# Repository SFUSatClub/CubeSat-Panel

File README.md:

# CubeSat Panel
KiCad project of the panels located on the outside of the spacecraft.

This repository uses the SFU Satellite Team's KiCad component library as a submodule.
To start working on the repository:

```
1. Open the git shell
2. Navigate to the directory you wish to place the repository inside
3. git clone --recursive "https://github.com/SFUSatClub/CubeSat-Panel.git"
4. cd CubeSat-Panel/KiCad-Lib
5. git checkout master
```

If you modify either the component schematic or footprint libraries you must push those changes to the SFUSatClub/KiCad-Lib repository.

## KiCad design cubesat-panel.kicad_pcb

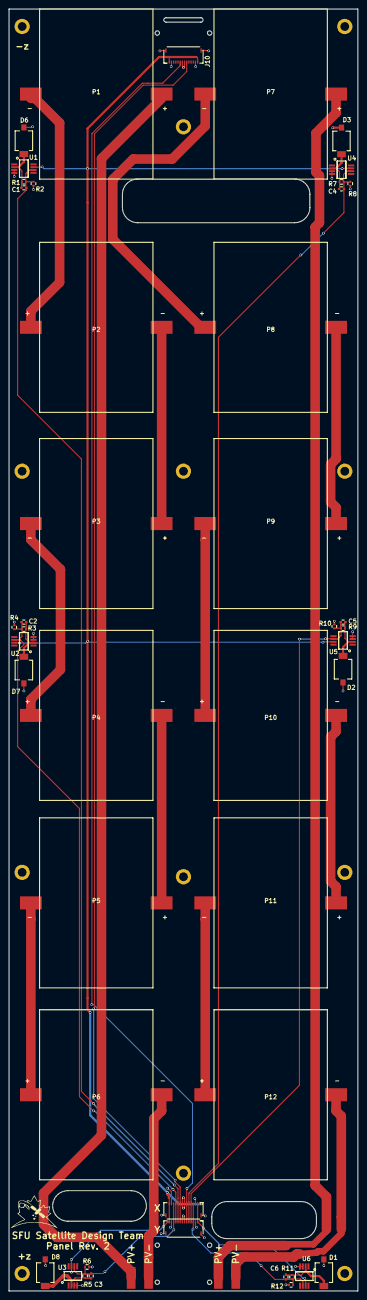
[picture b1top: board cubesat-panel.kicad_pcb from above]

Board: 2 copper layers, 80.0 x 294.0 mm, 61 parts (0 on the bottom side), 30 nets.

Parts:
C1, C2, C3, C4, C5, C6: 0.1uF; C_0402
D1, D2, D3, D4, D5, D6: D_Photo; SFH2430
J1, J2, J5, J6: CONN-TAB; CONN_TAB
J3, J9, J10: MOLEX_FFC-14
J11, J12, J13, J14, J15, J16, J17, J18, J19, J20, J21, J22: PC104PTH; PTH-2.0mm
P1, P2, P3, P4, P5, P6, P7, P8, P9, P10, P11, P12: JSLINTER; JSLINTER-39x26
R1, R3, R5, R7, R9, R11: 2K2; R_0402
R2, R4, R6, R8, R10, R12: DNP; R_0402
U1, U2, U3, U4, U5, U6: OPA380; VSSOP_8

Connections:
/3V3: J3.1, J3.14, J9.1, J9.14, J10.1, J10.14, U1.7, U2.7, U3.7, U4.7, U5.7, U6.7
/D1: C6.1, J3.12, J9.12, R11.1, R12.1, U6.6
/D2: C5.1, J3.11, J9.11, R9.1, R10.1, U5.6
/D3: C4.1, J3.10, J9.10, R7.1, R8.1, U4.6
/D6: C1.1, J3.5, J9.5, R1.1, R2.1, U1.6
/D7: C2.1, J3.4, J9.4, R3.1, R4.1, U2.6
/D8: C3.1, J3.3, J9.3, R5.1, R6.1, U3.6
/DA: J3.9, J9.9, J10.9
/DB: J3.6, J9.6, J10.6
/PV1+: J1.1, P1.1
/PV1-: J2.1, P6.2
/PV2+: J5.1, P7.1
/PV2-: J6.1, P12.2
GND: D1.2, D2.2, D3.2, D4.2, D5.2, D6.2, J3.2, J3.7, J3.8, J3.13, J3.SHLD, J9.2, J9.7, J9.8, J9.13, J9.SHLD, J10.2, J10.7, J10.8, J10.13, J10.SHLD, J11.1, J12.1, J13.1, J14.1, J15.1, J16.1, J17.1, J18.1, J19.1, J20.1, J21.1, J22.1, R2.2, R4.2, R6.2, R8.2, R10.2, R12.2, U1.3, U1.4, U2.3, U2.4, U3.3, U3.4, U4.3, U4.4, U5.3, U5.4, U6.3, U6.4
unnamed: C1.2, D1.1, R1.2, U1.2
unnamed: C2.2, D2.1, R3.2, U2.2
unnamed: C3.2, D3.1, R5.2, U3.2
unnamed: C4.2, D4.1, R7.2, U4.2
unnamed: C5.2, D5.1, R9.2, U5.2
unnamed: C6.2, D6.1, R11.2, U6.2
unnamed: P1.2, P2.1
unnamed: P2.2, P3.1
unnamed: P3.2, P4.1
unnamed: P4.2, P5.1
unnamed: P5.2, P6.1
unnamed: P7.2, P8.1
unnamed: P8.2, P9.1
unnamed: P9.2, P10.1
unnamed: P10.2, P11.1
unnamed: P11.2, P12.1

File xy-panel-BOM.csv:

reference,name,Digikey PN,Quantity
"J9,J10",MOLEX_FFC-14,WM1442CT-ND,2
D1,D_Photo,475-2579-1-ND,6
U1,OPA380,296-16860-1-ND,6
R1,2K2,P2.2KDCCT-ND,6
C1,0.1uF,445-14401-1-ND,6

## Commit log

2018-02-01 Began layout
2018-02-01 PV layout optimized for routing
2018-02-01 Added drawing of access panel
2018-02-04 Modified to single panel. To reduce integration complexity the formerly 3 panel configuration was changed to a single 300mm x 80mm board per side.
2018-02-05 Added README
2018-02-14 Layed out components. General layout of sun sensor sub system, PV, mounting hole, connectors, access panel cutout is complete. Yet to finalize ribbon cable signal layout and PV orientation.
2018-02-17 placed component values for amp feedback
2018-02-17 generated 3d model
2018-03-04 initial routing
2018-03-15 added new access cutout
2018-03-18 modified access panel geometry for new DC jacks, RBF, and Jtag, usb
2018-03-19 layout complete
2018-03-19 optimized silkscreen visibility, generated gerbers
2018-03-22 moved FFC position in accordance to PowerSystems Doc
2018-03-22 improved silkscreen labeling
2018-03-22 fixed dimentioning
2018-04-21 solder mask fixed to conform to min 150um webbing requirement
2018-04-21 updated fab notes
2018-06-02 updated pdf
2018-06-04 rev 2 done
